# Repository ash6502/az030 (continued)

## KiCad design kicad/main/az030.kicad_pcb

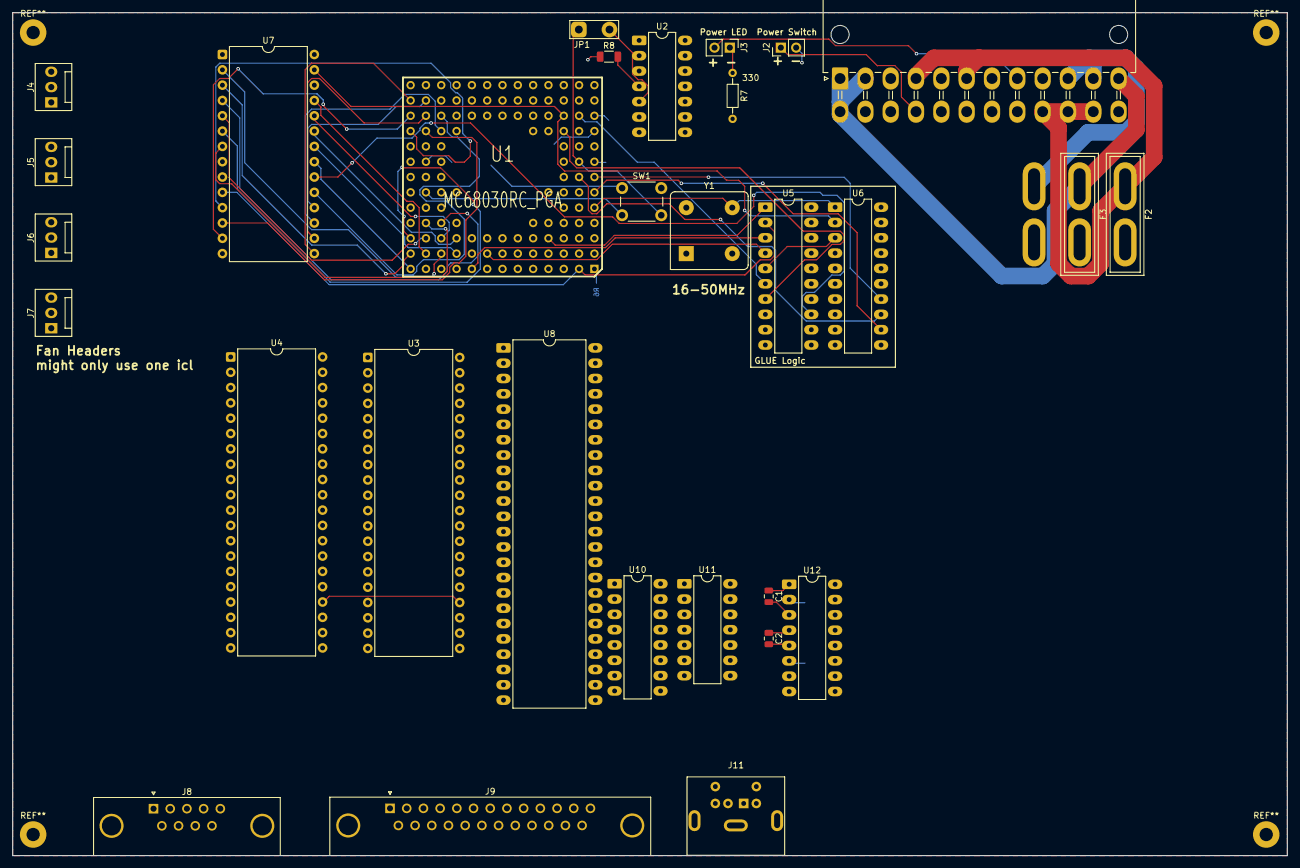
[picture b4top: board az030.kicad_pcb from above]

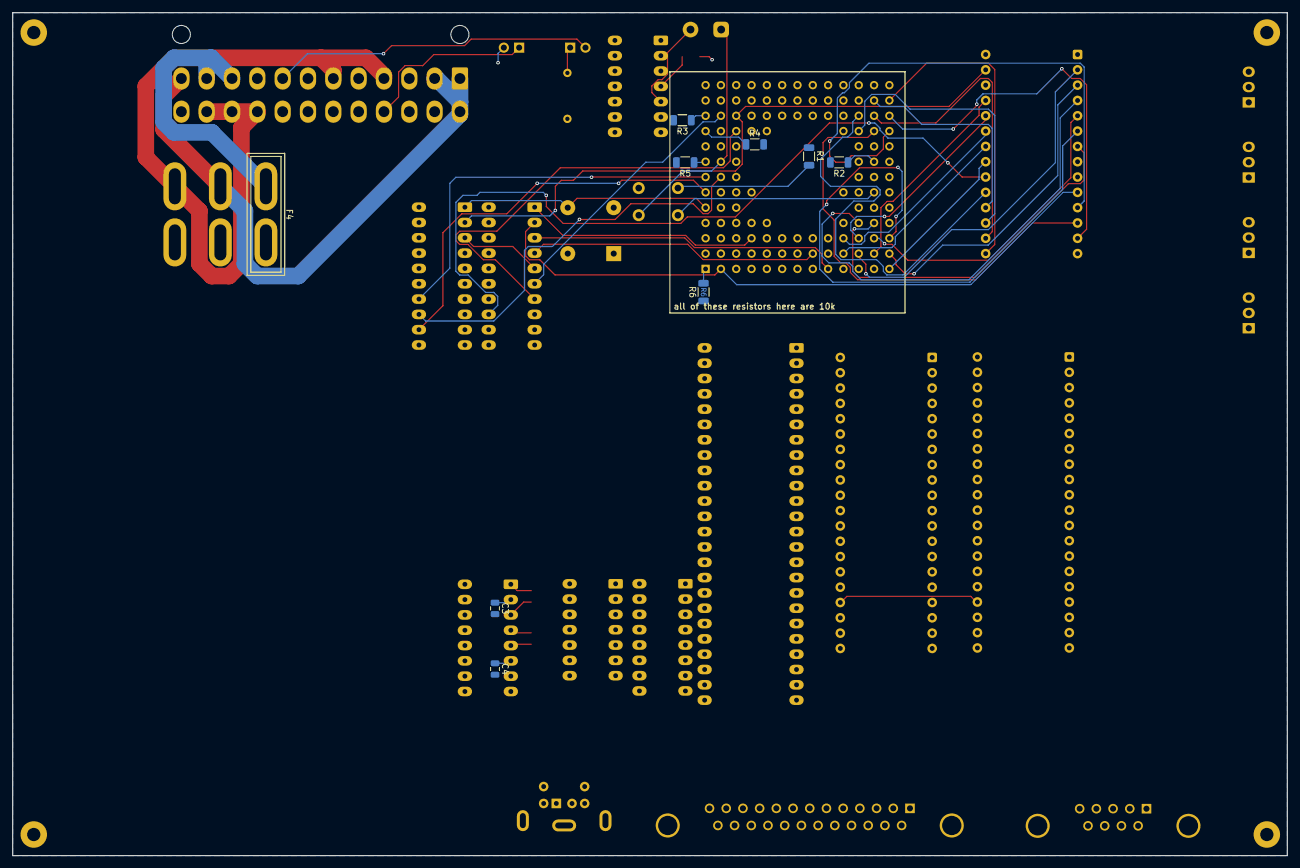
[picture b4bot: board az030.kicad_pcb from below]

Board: 4 copper layers, 211.4 x 139.8 mm, 39 parts (9 on the bottom side), 68 nets.

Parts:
C1, C2, C3, C4: 1u; C_0805_2012Metric
F2: 5a; Fuse_Blade_ATO_directSolder
F3, F4: 3a; Fuse_Blade_ATO_directSolder
J1: ATX-24; Molex_Mini-Fit_Jr_5569-24A2_2x12_P4.20mm_Horizontal
J2: Conn_01x02_Pin; PinHeader_1x02_P2.54mm_Vertical
J3: LED; PinHeader_1x02_P2.54mm_Vertical
J4, J5, J6, J7: Conn_01x03_Pin; FanPinHeader_1x03_P2.54mm_Vertical
J8: DE9_Pins_MountingHoles; DSUB-9_Pins_Horizontal_P2.77x2.84mm_EdgePinOffset4.94mm_Hou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
J9: DB25_Pins_MountingHoles; DSUB-25_Pins_Horizontal_P2.77x2.84mm_EdgePinOffset4.94mm_Ho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
J11: PS/2; Connector_Mini-DIN_Female_6Pin_2rows
JP1: RUN; TestPoint_2Pads_Pitch5.08mm_Drill1.3mm
R1, R2, R3, R4, R5, R6, R8: 10k; R_1206_3216Metric
R7: 330; R_Axial_DIN0204_L3.6mm_D1.6mm_P7.62mm_Horizontal
SW1: SW_Push; SW_PUSH_6mm
U1: MC68030RC_PGA; MC68030
U2: 74HC74; DIP-14_W7.62mm_LongPads
U3, U4: W65C22SxP; DIP-40_W15.24mm
U5, U6: GAL16V8; DIP-20_W7.62mm_LongPads
U7: CY62256-70PC; DIP-28_W15.24mm
U8: DIP-48_W15.24mm_LongPads
U10: 74AHC595; DIP-16_W7.62mm_LongPads
U11: 74AHC04; DIP-14_W7.62mm_LongPads
U12: MAX232; DIP-16_W7.62mm_LongPads
Y1: CXO_DIP8; Oscillator_DIP-8_LargePads

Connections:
+5V: F2.2, J11.4, R1.1, R2.2, R3.2, R4.2, R5.2, R6.1, R8.1, U1.C6 (VCC), U1.D4 (VCC), U1.D10 (VCC), U1.F2 (VCC), U1.F11 (VCC), U1.H3 (VCC), U1.H11 (VCC), U1.H13 (IPL0), U1.K4 (VCC), U1.K10 (VCC), U1.L6 (VCC), U2.14 (VCC), U3.20 (VCC), U4.20 (VCC), U5.20 (V_{CC}), U6.20 (V_{CC}), U7.28 (VCC), U10.10 (~SRCLR), U10.16 (VCC), U11.14 (VCC), U12.16 (VCC), Y1.8 (Vcc)
+12V: F4.2, J4.2, J5.2, J6.2, J7.2
/CPU/A0: U1.A2 (A0), U5.2 (I_{1}), U7.10 (A0)
/CPU/A1: U1.C4 (A1), U5.1 (I_{0}), U7.9 (A1)
/CPU/A2: U1.D13 (A2), U7.8 (A2)
/CPU/A3: U1.D12 (A3), U7.7 (A3)
/CPU/A4: U1.C13 (A4), U7.6 (A4)
/CPU/A5: U1.C12 (A5), U7.5 (A5)
/CPU/A6: U1.D11 (A6), U7.4 (A6)
/CPU/A7: U1.B13 (A7), U7.3 (A7)
/CPU/A8: U1.B12 (A8), U7.25 (A8)
/CPU/A9: U1.C11 (A9), U7.24 (A9)
/CPU/A10: U1.A13 (A10), U7.21 (A10)
/CPU/A11: U1.C10 (A11), U7.23 (A11)
/CPU/A12: U1.B11 (A12), U7.2 (A12)
/CPU/A13: U1.A12 (A13), U7.26 (A13)
/CPU/A14: U1.B10 (A14), U7.1 (A14), U7.22 (~OE)
/CPU/A19: U1.A9 (A19), U5.3 (I_{2})
/CPU/A20: U1.B8 (A20), U5.4 (I_{3})
/CPU/A25: U1.B6 (A25), U5.5 (I_{4}), U6.3 (I_{2})
/CPU/D0: U1.K13 (D0), U7.11 (Q0)
/CPU/D1: U1.K12 (D1), U7.12 (Q1)
/CPU/D2: U1.L13 (D2), U7.13 (Q2)
/CPU/D3: U1.M13 (D3), U7.15 (Q3)
/CPU/D4: U1.L12 (D4), U7.16 (Q4)
/CPU/D5: U1.K11 (D5), U7.17 (Q5)
/CPU/D6: U1.M12 (D6), U7.18 (Q6)
/CPU/D7: U1.L11 (D7), U7.19 (Q7)
/Peripheral Management/R~W: U3.22 (R/~W), U4.22 (R/~W)
AS: U1.J2 (AS), U5.8 (I_{7})
CLOCK: U1.E1 (CLKIN), U6.1 (I_{0}), Y1.5 (OUT)
DSACK0: U1.F1 (DSACK0), U6.12 (F_{0})
DSACK1: U1.G2 (DSACK1), U6.13 (F_{1})
ECS: U1.M2 (ECS), U2.3 (C)
GND: C3.2, C4.2, J1.3 (GND), J1.5 (GND), J1.7 (GND), J1.15 (GND), J1.17 (GND), J1.18 (GND), J1.19 (GND), J1.24 (GND), J2.2, J4.1, J5.1, J6.1, J7.1, J11.3, R7.2, U1.C5 (GND), U1.C7 (GND), U1.C9 (GND), U1.E2 (AVEC), U1.E3 (GND), U1.E11 (GND), U1.F3 (GND), U1.G3 (GND), U1.G11 (GND), U1.J3 (GND), U1.J11 (GND), U1.L5 (GND), U1.L7 (GND), U1.L8 (GND), U1.L9 (GND), U2.7 (GND), U3.1 (VSS), U4.1 (VSS), U5.10 (GND), U6.10 (GND), U7.14 (GND), U10.8 (GND), U10.13 (~OE), U11.7 (GND), U12.15 (GND), Y1.4 (GND)
unnamed: F2.1, J1.4 (+5V), J1.6 (+5V), J1.21 (+5V), J1.22 (+5V), J1.23 (+5V)
unnamed: F3.1, J1.1 (+3.3V), J1.2 (+3.3V), J1.12 (+3.3V), J1.13 (+3.3V)
unnamed: F4.1, J1.10 (+12V), J1.11 (+12V)
unnamed: J1.16 (PS_ON#), J2.1
unnamed: J1.8 (PWR_OK), J3.2
unnamed: J3.1, R7.1
unnamed: JP1.1 (A), U1.H2 (HLT)
unnamed: JP1.2 (B), U2.5 (Q)
unnamed: R5.1, U1.H1 (BERR)
unnamed: R6.2, U1.A1 (BR)
unnamed: R4.1, U1.K1 (CBREQ)
unnamed: R2.1, U1.H12 (CDIS)
unnamed: R3.1, U1.L1 (CIIN)
unnamed: SW1.2, U1.F12 (RESET)
unnamed: U2.2 (D), U2.6 (~Q)
unnamed: R8.2, U2.4 (~S)
unnamed: U10.12 (RCLK), U11.6
unnamed: U10.11 (SRCLK), U11.2, U11.3
unnamed: U11.4, U11.5
unnamed: C1.1, U12.1 (C1+)
unnamed: C1.2, U12.3 (C1-)
unnamed: C2.1, U12.4 (C2+)
unnamed: C2.2, U12.5 (C2-)
unnamed: C3.1, U12.2 (VS+)
unnamed: C4.1, U12.6 (VS-)
PS/2 Clock: J11.5, U11.1
PS/2 Data: J11.1, U10.14 (SER)
RAM0: U5.13 (F_{1}), U7.20 (~CS)
RESET: R1.2, SW1.1, U2.1 (~R), U8.2 (RST_2)
R~W: U1.L3 (R_W), U6.2 (I_{1}), U7.27 (~WE)
SIZ0: U1.L2 (SIZ0), U5.6 (I_{5})
SIZ1: U1.K3 (SIZ1), U5.7 (I_{6})
STERM: U1.G1 (STERM), U6.14 (F_{2})
